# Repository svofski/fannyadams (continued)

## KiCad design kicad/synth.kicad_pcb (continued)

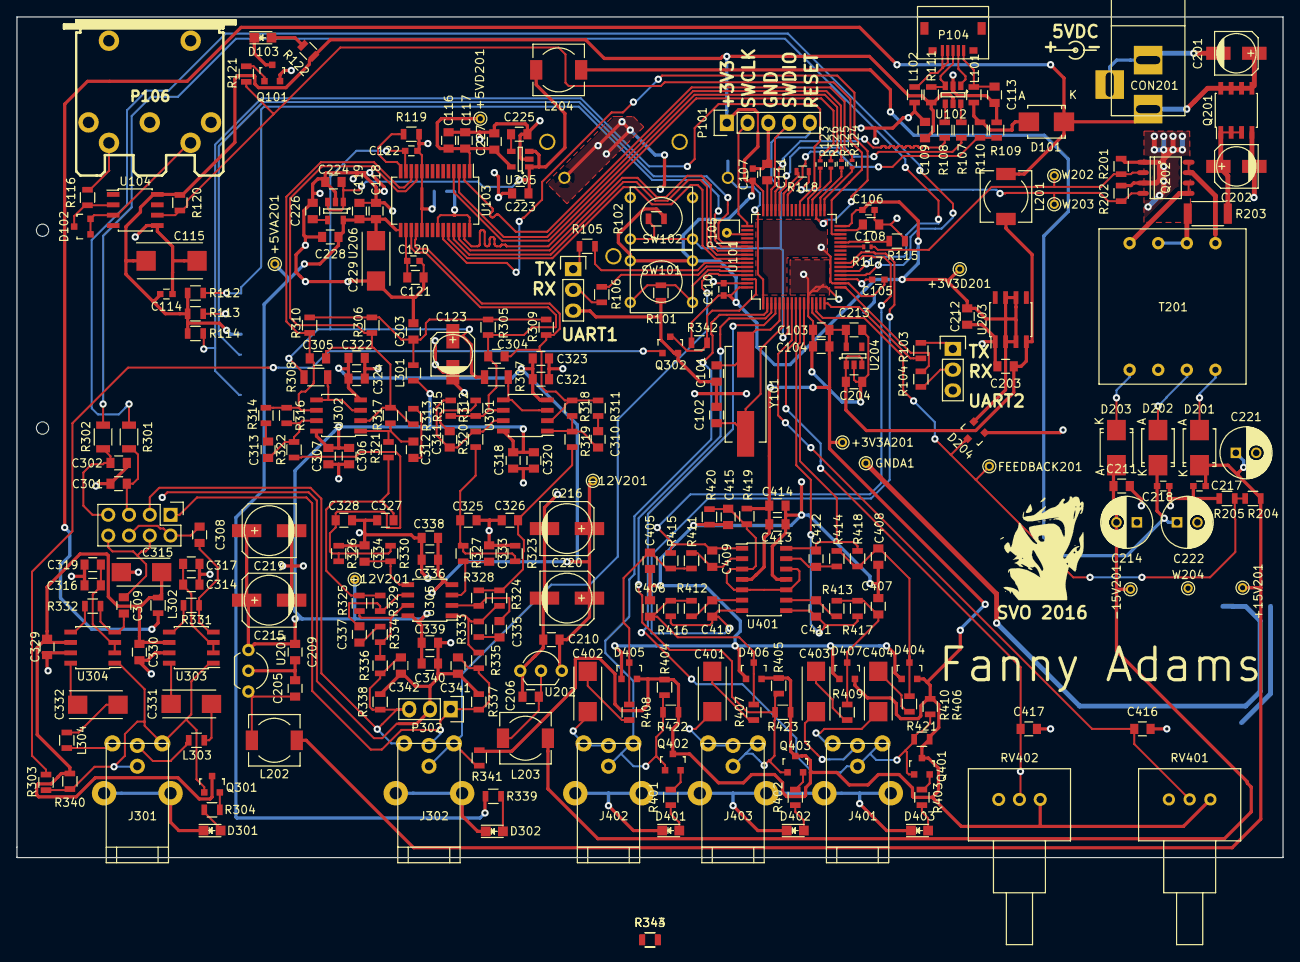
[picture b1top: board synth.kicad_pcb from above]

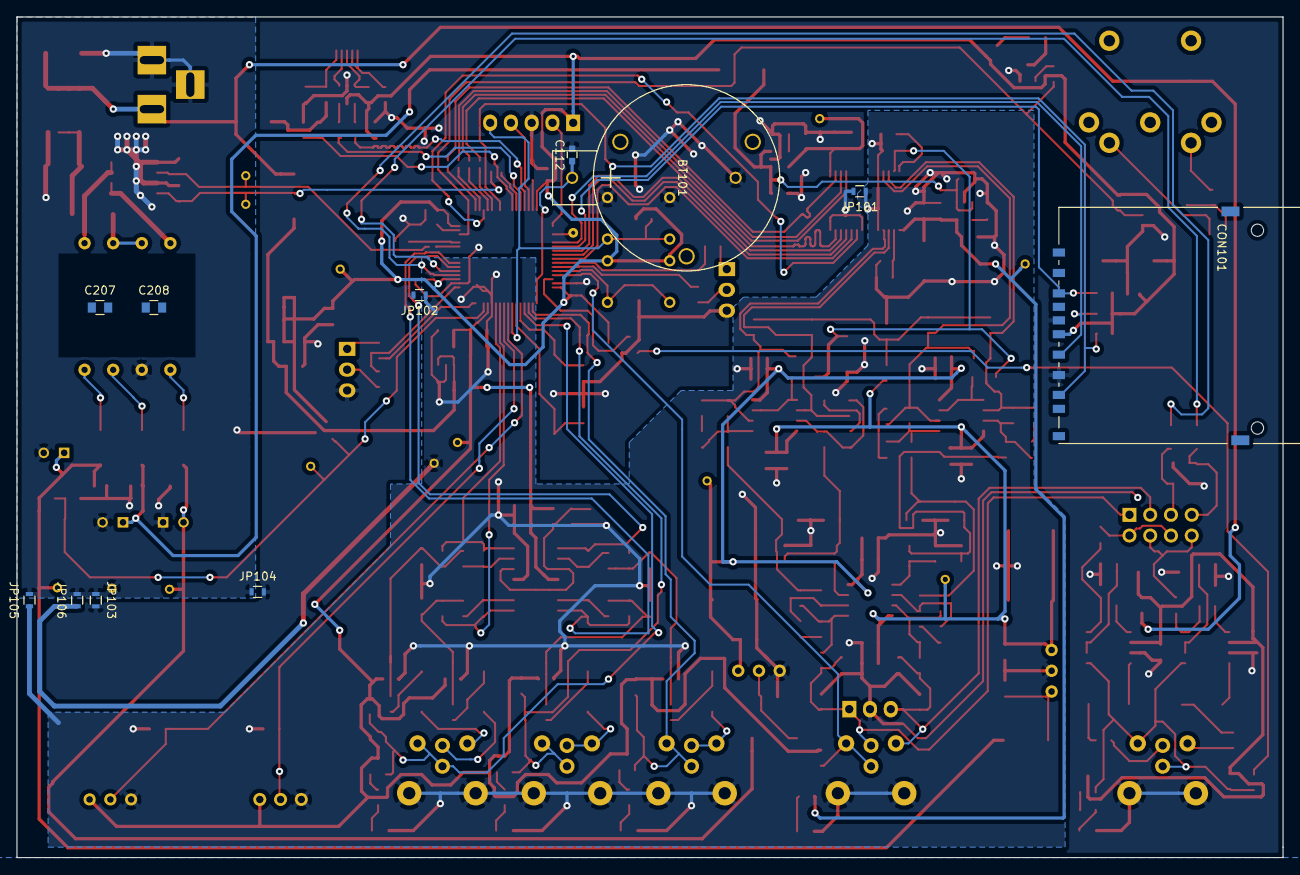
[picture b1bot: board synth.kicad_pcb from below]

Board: 2 copper layers, 154.9 x 102.9 mm, 300 parts (11 on the bottom side), 174 nets.

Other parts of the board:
R343, R344: 20K; R_0805

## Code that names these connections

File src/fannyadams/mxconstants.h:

/**
  ******************************************************************************
  * File Name          : mxconstants.h
  * Description        : This file contains the common defines of the application
  ******************************************************************************
  *
  * COPYRIGHT(c) 2015 STMicroelectronics
  *
  * Redistribution and use in source and binary forms, with or without modification,
  * are permitted provided that the following conditions are met:
  *   1. Redistributions of source code must retain the above copyright notice,
  *      this list of conditions and the following disclaimer.
  *   2. Redistributions in binary form must reproduce the above copyright notice,
  *      this list of conditions and the following disclaimer in the documentation
  *      and/or other materials provided with the distribution.
  *   3. Neither the name of STMicroelectronics nor the names of its contributors
  *      may be used to endorse or promote products derived from this software
  *      without specific prior written permission.
  *
  * THIS SOFTWARE IS PROVIDED BY THE COPYRIGHT HOLDERS AND CONTRIBUTORS "AS IS"
  * AND ANY EXPRESS OR IMPLIED WARRANTIES, INCLUDING, BUT NOT LIMITED TO, THE
  * IMPLIED WARRANTIES OF MERCHANTABILITY AND FITNESS FOR A PARTICULAR PURPOSE ARE
  * DISCLAIMED. IN NO EVENT SHALL THE COPYRIGHT HOLDER OR CONTRIBUTORS BE LIABLE
  * FOR ANY DIRECT, INDIRECT, INCIDENTAL, SPECIAL, EXEMPLARY, OR CONSEQUENTIAL
  * DAMAGES (INCLUDING, BUT NOT LIMITED TO, PROCUREMENT OF SUBSTITUTE GOODS OR
  * SERVICES; LOSS OF USE, DATA, OR PROFITS; OR BUSINESS INTERRUPTION) HOWEVER
  * CAUSED AND ON ANY THEORY OF LIABILITY, WHETHER IN CONTRACT, STRICT LIABILITY,
  * OR TORT (INCLUDING NEGLIGENCE OR OTHERWISE) ARISING IN ANY WAY OUT OF THE USE
  * OF THIS SOFTWARE, EVEN IF ADVISED OF THE POSSIBILITY OF SUCH DAMAGE.
  *
  ******************************************************************************
  */
/* Includes ------------------------------------------------------------------*/

/* USER CODE BEGIN Includes */

/* USER CODE END Includes */

/* Private define ------------------------------------------------------------*/

#define PLUG1_Pin GPIO_PIN_13
#define PLUG1_GPIO_Port GPIOC
#define PLUG2_Pin GPIO_PIN_14
#define PLUG2_GPIO_Port GPIOC
#define PLUG3_Pin GPIO_PIN_15
#define PLUG3_GPIO_Port GPIOC

#define ADC3_IN10_POT1_Pin GPIO_PIN_0
#define ADC3_IN10_POT1_GPIO_Port GPIOC
#define ADC3_IN11_POT2_Pin GPIO_PIN_1
#define ADC3_IN11_POT2_GPIO_Port GPIOC

#define ADC1_IN12_L_Pin GPIO_PIN_2
#define ADC1_IN12_L_GPIO_Port GPIOC
#define ADC2_IN13_R_Pin GPIO_PIN_3
#define ADC2_IN13_R_GPIO_Port GPIOC
#define ADC3_IN0_PWM_FB_Pin GPIO_PIN_0
#define ADC3_IN0_PWM_FB_GPIO_Port GPIOA
  
#define ADC1_IN6_HIGAIN1_Pin GPIO_PIN_6
#define ADC1_IN6_HIGAIN1_GPIO_Port GPIOA
#define ADC2_IN7_HIGAIN2_Pin GPIO_PIN_7
#define ADC2_IN7_HIGAIN2_GPIO_Port GPIOA
#define PWM_PULL_Pin GPIO_PIN_1
#define PWM_PULL_GPIO_Port GPIOB
#define USART3_RX_MIDI_IN_Pin GPIO_PIN_11
#define USART3_RX_MIDI_IN_GPIO_Port GPIOB
#define DACRST_Pin GPIO_PIN_14
#define DACRST_GPIO_Port GPIOB
#define PHONES_ENA_Pin GPIO_PIN_7
#define PHONES_ENA_GPIO_Port GPIOC
#define LEDPLUG2_Pin GPIO_PIN_9
#define LEDPLUG2_GPIO_Port GPIOC
#define LEDPLUG3_Pin GPIO_PIN_8
#define LEDPLUG3_GPIO_Port GPIOA
#define PWM_PUSH_Pin GPIO_PIN_10
#define PWM_PUSH_GPIO_Port GPIOA
#define LEDPLUG1_Pin GPIO_PIN_11
#define LEDPLUG1_GPIO_Port GPIOC
#define DAC_CS_Pin GPIO_PIN_4
#define DAC_CS_GPIO_Port GPIOB
#define LINEOUT_SW_Pin GPIO_PIN_8
#define LINEOUT_SW_GPIO_Port GPIOB
#define PHONES_SW_Pin GPIO_PIN_9
#define PHONES_SW_GPIO_Port GPIOB
/* USER CODE BEGIN Private defines */

/* USER CODE END Private defines */

/**
  * @}
  */ 

/**
  * @}
*/ 

/************************ (C) COPYRIGHT STMicroelectronics *****END OF FILE****/

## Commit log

2015-12-16 :space_invader: Added .gitattributes & .gitignore files
2015-12-16 booobooo
2015-12-20 before moving headphone amp to the left
2015-12-21 gruuuu
2015-12-21 drc ok large vias
2015-12-21 ok
    adding inline resistors on i2s next
2015-12-21 battery is on the wrong side... sigh
2015-12-22 version sent to rezonit
    modified usb connector pads to smd
2015-12-28 fixed p-mosfets
2015-12-29 fuck hal
2015-12-29 fixed prototypes
2015-12-29 adc3 with dam
2015-12-30 tim1 complementary pwm + rudimentary duty cycle adjustment using dead-time
2015-12-30 cleanup of tim1 code
2015-12-30 tabs
2016-01-03 power management works, dc-dc needs tuning
2016-01-05 circuit fixes
2016-01-09 audio sink works
2016-01-09 audio source graph builds ok
2016-01-09 usb sawtooth "microphone" works
2016-01-09 - temporarily disabled recording interface because osx is fucked up and bangs it while playing back sound - playback produces awful distortion, some receive/dac buffer synch is needed
2016-01-09 works but with awesome phasor effect due to iso desync
2016-01-23 the shit is fucked basically, although implicit feedback works well on OSX. windows cares buggerall about implicit feedback
2016-01-24 async with explicit feedback works on mac, when it picks it up. windows is still shit
2016-01-24 explicit async feedback works on windows (like on mac, not every time)
2016-01-24 a bit of cleaning up
2016-01-24 tried to define interfaces and ep numbers with some flexibility
2016-01-24 a bit more cleanup
2016-01-24 project
2016-01-24 trying to enforce spaces
2016-01-24 spaces...
2016-01-24 CDC works again, renumbered all endpoints for both cases
2020-01-05 CDC + Audio enumerates under windows
    * removed libopencm3 as submodule: ref usbaudio branch in my repo
    * experimental tweaks with volume
    * implemented mute control by zeroing out samples
    * cdc only does distorted echo
    * not sure but debug uart doesn't seem to be working, could be a faulty
    usb serial dongle
2020-01-05 renamed file
2020-01-10 cdc vcp debugging works ok
    no need for usb serial dongles!
2020-01-25 enumerates fine but doesn't wrok
2020-01-25 midi enumerates, audio works
    midi receives one message and the midi ends there
2020-01-26 read from the correct endpoint ~\_('/' )_/~
2020-01-26 some midi messages parsing
    note on,note off, pitch bend, cc/sound off
2020-01-27 moved audio buffer to audiobuf.h
    trying to make the initial hack more manageable
2020-01-28 reformat with clang-format
2020-01-30 audio + midi works
    audible aliasing on the sine wave, maybe 256 samples is not enough
2020-01-30 multiple oscillators experiment
    apparently 16 oscillators is already a problem. hmm?
2020-01-30 adsr and some new tests
    useful for verifying the algorithms on the pc
2020-01-30 cool sixel test runner
2020-02-04 plays midi file
    * all with a single adsr
    * all with the same sin oscillator
    * all with the same volume
    * floats seem to work well on M4 so it's all float
    * initial 1s delay hacked in -- not sure what's going on there but
    while enumerating it's better to stay clear of synthing -- posisbly
2020-02-04 support midi velocity->volume and panic commands
2020-02-05 jacks can be replugged multiple times
    cm_disable_interrupts() appears to kill the main loop somehow.
    there is no real need to disable interrupts there, so there.
2020-02-07 implemented triangle, saw, pwm
2020-02-13 implemented program change and some lame patches
    * fixed pitchbend
    * patches are just foolery with adsr and waveforms
2020-02-14 linux emulator wrapped in alsa
    allows developing the synth engine on a pc without stm32 board
    running the emulator creates a midi synth device in linux
    connect vmpk:
    aconnect 129:0 128:0
    play a midi:
    pmidi -p 128:0 yehat.mid
